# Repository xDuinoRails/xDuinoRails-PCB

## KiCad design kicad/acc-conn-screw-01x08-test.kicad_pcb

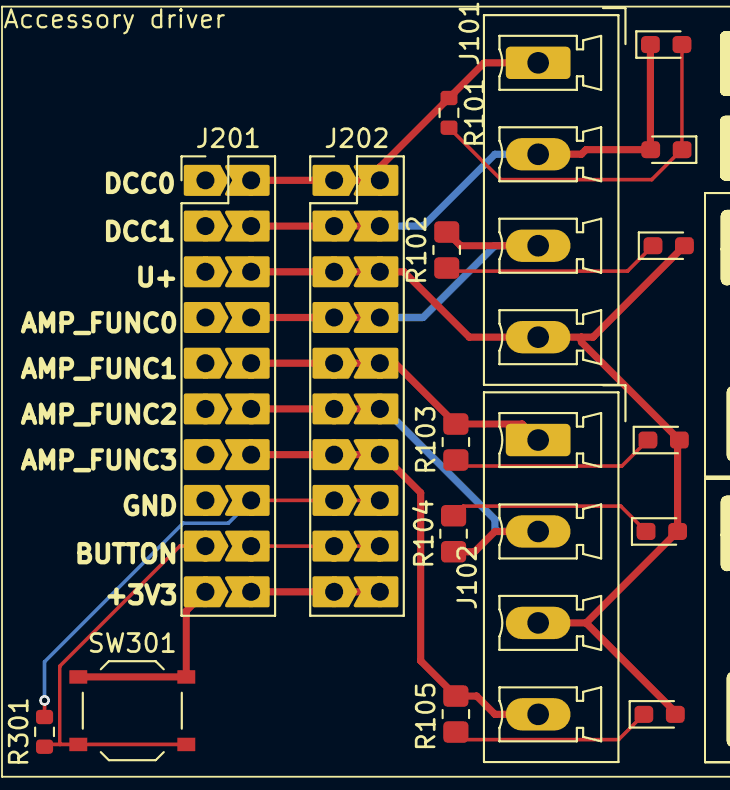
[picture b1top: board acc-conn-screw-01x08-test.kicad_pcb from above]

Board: 2 copper layers, 17 parts (0 on the bottom side), 17 nets.

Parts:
D101: LED_YELLOW; LED_0603_1608Metric_Pad1.05x0.95mm_HandSolder
D102: LED_WHITE; LED_0603_1608Metric_Pad1.05x0.95mm_HandSolder
D103, D105: LED_RED; LED_0603_1608Metric_Pad1.05x0.95mm_HandSolder
D104, D106: LED_GREEN; LED_0603_1608Metric_Pad1.05x0.95mm_HandSolder
J101, J102: Conn_01x04; PhoenixContact_MCV_1,5_4-G-5.08_1x04_P5.08mm_Vertical
J201, J202: Conn_02x10_Odd_Even; PinHeaderJP_2x10_P2.54mm_Vertical
R101, R301: 10k; R_0603_1608Metric
R102, R103, R104, R105: 1k; R_0805_2012Metric_Pad1.20x1.40mm_HandSolder
SW301: TS-1187A-B-A-B; SW_Push_1P1T_XKB_TS-1187A

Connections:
/+3V3: J201.19, SW301.1
/BUTTON: J201.17, R301.1, SW301.2
/J_+3V3: J201.20, J202.19, J202.20
/J_AMP_FUNC0: J101.3, J201.8, J202.7, J202.8, R102.1
/J_AMP_FUNC1: J102.1, J201.10, J202.9, J202.10, R103.1
/J_AMP_FUNC2: J102.2, J201.12, J202.11, J202.12, R104.1
/J_AMP_FUNC3: J102.4, J201.14, J202.13, J202.14, R105.1
/J_BUTTON: J201.18, J202.17, J202.18
/J_DCC0: J101.1, J201.2, J202.1, J202.2, R101.1
/J_DCC1: D101.2 (A), D102.1 (K), J101.2, J201.4, J202.3, J202.4
/J_GND: J201.16, J202.15, J202.16, R301.2
/J_U+: D103.2 (A), D104.2 (A), D105.2 (A), D106.2 (A), J101.4, J102.3, J201.6, J202.5, J202.6
unnamed: D101.1 (K), D102.2 (A), R101.2
unnamed: D103.1 (K), R102.2
unnamed: D104.1 (K), R103.2
unnamed: D105.1 (K), R104.2
unnamed: D106.1 (K), R105.2

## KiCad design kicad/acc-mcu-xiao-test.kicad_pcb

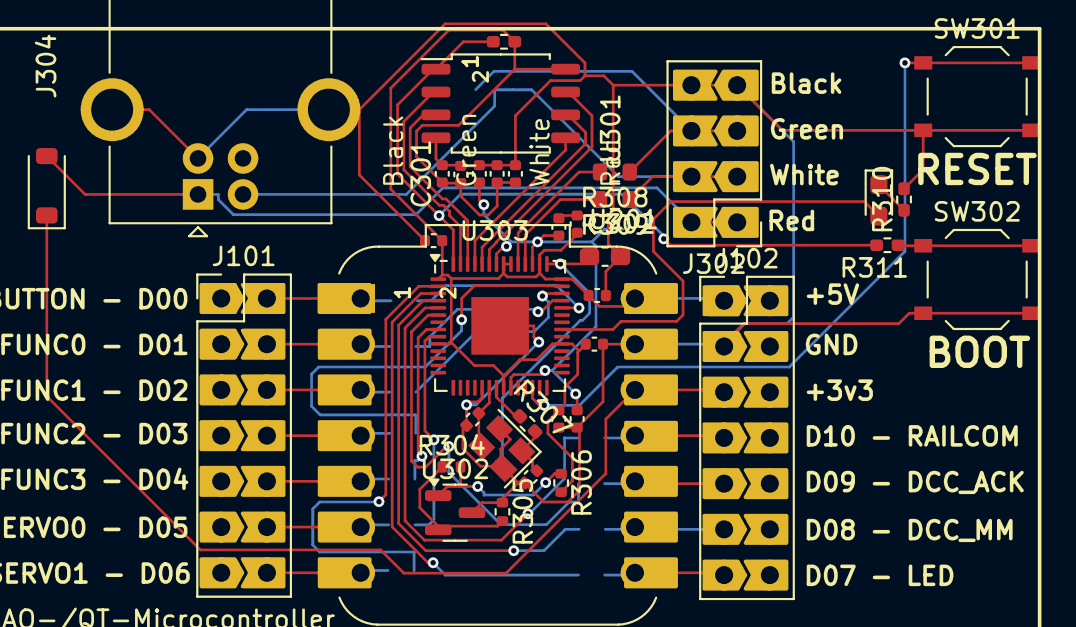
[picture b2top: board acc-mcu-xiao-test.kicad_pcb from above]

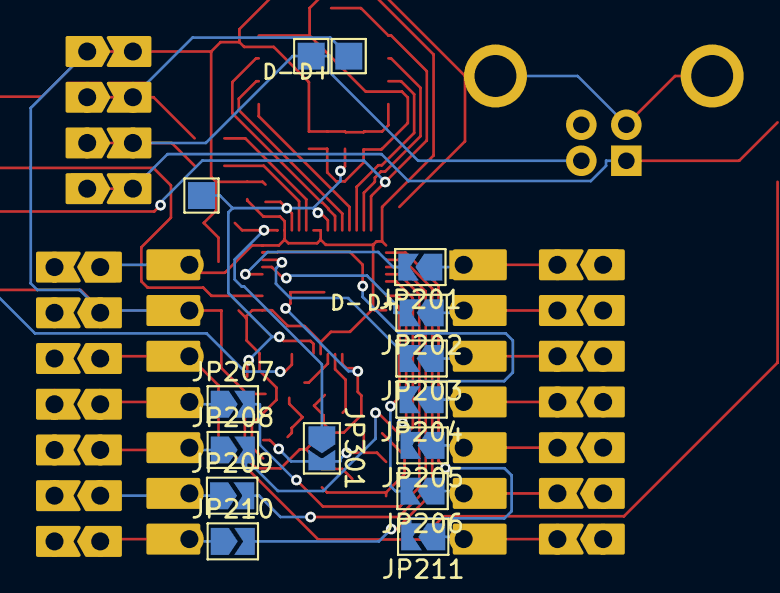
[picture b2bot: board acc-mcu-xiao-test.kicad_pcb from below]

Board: 2 copper layers, 52 parts (15 on the bottom side), 47 nets.

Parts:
C301, C305, C306, C308, C310, C311, C312, C313, C314, C315: 100n; C_0402_1005Metric
C302: 10n C0G; C_0603_1608Metric_Pad1.08x0.95mm_HandSolder
C303, C304: 18p; C_0402_1005Metric
C307, C309: 1u; C_0402_1005Metric
D301: B5819W; D_SOD-123
D302: LED; LED_0603_1608Metric_Pad1.05x0.95mm_HandSolder
J101, J102: Conn_02x07_Odd_Even; PinHeaderJP_2x07_P2.54mm_Vertical
J302: Conn_02x04_Odd_Even; PinHeaderJP_2x04_P2.54mm_Vertical
J304: USB_B; USB_B_OST_USB-B1HSxx_Horizontal
JP201, JP202, JP203, JP204, JP205, JP206, JP207, JP208, JP209, JP210, JP211: SolderJumper_2_Open; SolderJumper-2_P1.3mm_Open_TrianglePad1.0x1.5mm
JP301: VREF; SolderJumper-2_P1.3mm_Open_TrianglePad1.0x1.5mm
R301: DNP; R_0402_1005Metric_Pad0.72x0.64mm_HandSolder
R304: 680R; R_0402_1005Metric
R305: 3k3; R_0402_1005Metric
R306: 150R; R_0402_1005Metric
R307, R310, R311: 1k; R_0402_1005Metric_Pad0.72x0.64mm_HandSolder
R308, R309: 27R; R_0603_1608Metric
SW301: RESET; SW_Push_1P1T_XKB_TS-1187A
SW302: BOOTSEL; SW_Push_1P1T_XKB_TS-1187A
TP301: VREG; TestPoint_Pad_1.5x1.5mm
TP302: D+; TestPoint_Pad_1.5x1.5mm
TP303: D-; TestPoint_Pad_1.5x1.5mm
U201: MOUDLE-SEEEDUINO-XIAO-ESP32C3; XIAO_THT_SMD
U301: W25Q128JVSIQ; SOIC-8_5.23x5.23mm_P1.27mm
U302: TL431DBZ; SOT-23
U303: RP2040; QFN-56-1EP_7x7mm_P0.4mm_EP3.2x3.2mm
Y301: ECS-120-12-36-AGN-TR3; Crystal_SMD_2520-4Pin_2.5x2.0mm

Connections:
+1V1: C305.1, C306.1, C307.1, TP301.1, U303.23 (DVDD), U303.45 (VREG_VOUT), U303.50 (DVDD)
+5V: D301.1 (K), J102.5, U201.12 (3V3)
/J_+3v3: C301.1, C308.1, C309.1, C310.1, C311.1, C312.1, C313.1, C314.1, C315.1, J102.1, R301.1, R306.2, U201.14 (5V), U301.8 (VCC), U303.1 (IOVDD), U303.10 (IOVDD), U303.22 (IOVDD), U303.33 (IOVDD), U303.42 (IOVDD), U303.44 (VREG_IN), U303.48 (USB_VDD), U303.49 (IOVDD)
/J_BUTTON: J101.2, JP201.1 (A), U201.1 (A0)
/J_DCC_ACK: J102.11, JP209.1 (A), U201.9 (A8_SCK)
/J_DCC_MM: J102.13, JP210.1 (A), U201.8 (A7_RX)
/J_FUNC0: J101.4, JP202.1 (A), U201.2 (A1)
/J_FUNC1: J101.6, JP203.1 (A), U201.3 (A2)
/J_FUNC2: J101.8, JP204.1 (A), U201.4 (A3)
/J_FUNC3: J101.10, JP205.1 (A), U201.5 (A4_SDA)
/J_GND: C301.2, C302.2, C303.2, C304.2, C305.2, C306.2, C307.2, C308.2, C309.2, C310.2, C311.2, C312.2, C313.2, C314.2, C315.2, J102.3, J302.7, J302.8, J304.4 (GND), J304.5 (Shield), R305.1, R310.2, SW301.2, SW302.2, U201.13 (GND), U301.4 (GND), U302.3 (A), U303.19 (TESTEN), U303.57 (GND), Y301.2, Y301.4
/J_LED: J102.7, JP207.1 (A), U201.11 (A10_MOSI)
/J_RAILCOM: J102.9, JP208.1 (A), U201.10 (A9_MISO)
/J_SERVO0: J101.12, JP206.1 (A), U201.6 (A5_SCL)
/J_SERVO1: J101.14, JP211.1 (A), U201.7 (A6_TX)
/acc-mcu-xiao/GPIO0: JP211.2 (B), U303.2 (GPIO0)
/acc-mcu-xiao/GPIO1: JP210.2 (B), U303.3 (GPIO1)
/acc-mcu-xiao/GPIO2: JP209.2 (B), U303.4 (GPIO2)
/acc-mcu-xiao/GPIO3: JP207.2 (B), U303.5 (GPIO3)
/acc-mcu-xiao/GPIO4: JP208.2 (B), U303.6 (GPIO4)
/acc-mcu-xiao/GPIO6: JP205.2 (B), U303.8 (GPIO6)
/acc-mcu-xiao/GPIO7: JP206.2 (B), U303.9 (GPIO7)
/acc-mcu-xiao/GPIO23: D302.2 (A), U303.35 (GPIO23)
/acc-mcu-xiao/GPIO26: JP201.2 (B), U303.38 (GPIO26_ADC0)
/acc-mcu-xiao/GPIO27: JP202.2 (B), U303.39 (GPIO27_ADC1)
/acc-mcu-xiao/GPIO28: JP203.2 (B), U303.40 (GPIO28_ADC2)
/acc-mcu-xiao/GPIO29: JP204.2 (B), U303.41 (GPIO29_ADC3)
/acc-mcu-xiao/mcu_rp2040-onboard/2v5_VREF: R304.1, R305.2, U302.2 (REF)
/acc-mcu-xiao/mcu_rp2040-onboard/3V0_VREF: JP301.2 (B), R304.2, R306.1, U302.1 (K)
/acc-mcu-xiao/mcu_rp2040-onboard/ADC_VREF: C302.1, JP301.1 (A), U303.43 (ADC_AVDD)
/acc-mcu-xiao/mcu_rp2040-onboard/D+: J302.5, J302.6, R308.1, TP302.1
/acc-mcu-xiao/mcu_rp2040-onboard/D-: J302.3, J302.4, J304.2 (D-), R309.1, TP303.1
/acc-mcu-xiao/mcu_rp2040-onboard/DN: R309.2, U303.46 (USB_DM)
/acc-mcu-xiao/mcu_rp2040-onboard/DP: R308.2, U303.47 (USB_DP)
/acc-mcu-xiao/mcu_rp2040-onboard/QSPI_SCLK: U301.6 (CLK), U303.52 (QSPI_SCLK)
/acc-mcu-xiao/mcu_rp2040-onboard/QSPI_SD0: U301.5 (DI(IO0)), U303.53 (QSPI_SD0)
/acc-mcu-xiao/mcu_rp2040-onboard/QSPI_SD1: U301.2 (DO(IO1)), U303.55 (QSPI_SD1)
/acc-mcu-xiao/mcu_rp2040-onboard/QSPI_SD2: U301.3 (IO2), U303.54 (QSPI_SD2)
/acc-mcu-xiao/mcu_rp2040-onboard/QSPI_SD3: U301.7 (IO3), U303.51 (QSPI_SD3)
/acc-mcu-xiao/mcu_rp2040-onboard/QSPI_SS: R301.2, R311.1, U301.1 (~CS), U303.56 (QSPI_SS)
/acc-mcu-xiao/mcu_rp2040-onboard/RESET_RUN: SW301.1, U303.26 (RUN)
/acc-mcu-xiao/mcu_rp2040-onboard/XIN: C303.1, U303.20 (XIN), Y301.3
/acc-mcu-xiao/mcu_rp2040-onboard/XOUT: R307.1, U303.21 (XOUT)
unnamed: C304.1, R307.2, Y301.1
unnamed: D302.1 (K), R310.1
unnamed: R311.2, SW302.1
VBUS: D301.2 (A), J302.1, J302.2, J304.1 (VBUS)

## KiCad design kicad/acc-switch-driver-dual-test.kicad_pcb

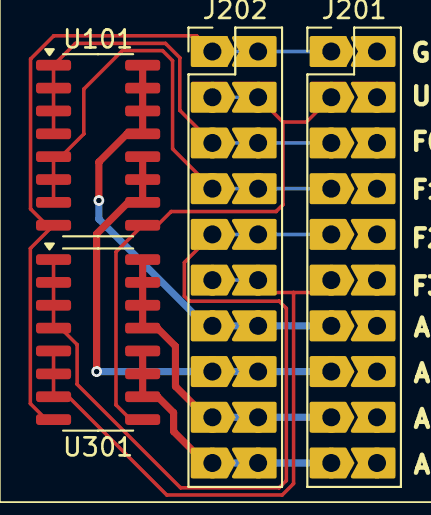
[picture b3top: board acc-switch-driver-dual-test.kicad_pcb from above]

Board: 2 copper layers, 4 parts (0 on the bottom side), 10 nets.

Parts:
J201, J202: Conn_02x10_Odd_Even; PinHeaderJP_2x10_P2.54mm_Vertical
U101, U301: ULN2003A; SOIC-16_3.9x9.9mm_P1.27mm

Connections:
/J_AMP_FUNC0: J201.13, J202.13, J202.14, U101.13 (O4), U101.14 (O3), U101.15 (O2), U101.16 (O1)
/J_AMP_FUNC1: J201.15, J202.15, J202.16, U101.10 (O7), U101.11 (O6), U101.12 (O5)
/J_AMP_FUNC2: J201.17, J202.17, J202.18, U301.13 (O4), U301.14 (O3), U301.15 (O2), U301.16 (O1)
/J_AMP_FUNC3: J201.19, J202.19, J202.20, U301.10 (O7), U301.11 (O6), U301.12 (O5)
/J_FUNC0: J201.5, J202.5, J202.6, U101.1 (I1), U101.2 (I2), U101.3 (I3), U101.4 (I4)
/J_FUNC1: J201.7, J202.7, J202.8, U101.5 (I5), U101.6 (I6), U101.7 (I7)
/J_FUNC2: J201.9, J202.9, J202.10, U301.1 (I1), U301.2 (I2), U301.3 (I3), U301.4 (I4)
/J_FUNC3: J201.11, J202.11, J202.12, U301.5 (I5), U301.6 (I6), U301.7 (I7)
/J_GND: J201.1, J202.1, J202.2, U101.8 (GND), U301.8 (GND)
/J_U+: J201.3, J202.3, J202.4, U101.9 (COM), U301.9 (COM)

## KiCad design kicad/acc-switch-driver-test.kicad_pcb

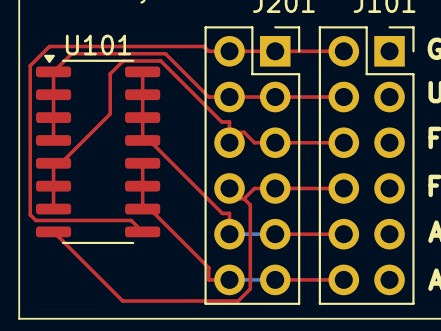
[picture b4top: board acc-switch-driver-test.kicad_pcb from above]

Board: 2 copper layers, 3 parts (0 on the bottom side), 6 nets.

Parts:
J101, J201: Conn_02x06_Odd_Even; PinSocket_2x06_P2.54mm_Vertical
U101: ULN2003A; SOIC-16_3.9x9.9mm_P1.27mm

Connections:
/J_AMP_FUNC0: J101.10, J201.9, J201.10, U101.13 (O4), U101.14 (O3), U101.15 (O2), U101.16 (O1)
/J_AMP_FUNC1: J101.12, J201.11, J201.12, U101.10 (O7), U101.11 (O6), U101.12 (O5)
/J_FUNC0: J101.4, J201.3, J201.4, U101.1 (I1), U101.2 (I2), U101.3 (I3), U101.4 (I4)
/J_FUNC1: J101.6, J201.5, J201.6, U101.5 (I5), U101.6 (I6), U101.7 (I7)
/J_GND: J101.8, J201.7, J201.8, U101.8 (GND)
/J_U+: J101.2, J201.1, J201.2, U101.9 (COM)

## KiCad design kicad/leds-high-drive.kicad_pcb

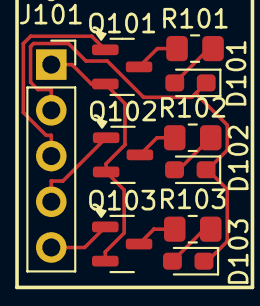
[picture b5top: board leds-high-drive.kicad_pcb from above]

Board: 2 copper layers, 10 parts (0 on the bottom side), 11 nets.

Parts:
D101: LED_RED; LED_0603_1608Metric_Pad1.05x0.95mm_HandSolder
D102: LED_YELLOW; LED_0603_1608Metric_Pad1.05x0.95mm_HandSolder
D103: LED_GREEN; LED_0603_1608Metric_Pad1.05x0.95mm_HandSolder
J101: Conn_01x05; PinSocket_1x05_P2.54mm_Vertical
Q101, Q102, Q103: S8550; 8x50_SOT-23
R101, R102, R103: 1k; R_0805_2012Metric_Pad1.20x1.40mm_HandSolder

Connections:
/+3v3: J101.1, Q101.1 (E), Q102.1 (E), Q103.1 (E)
/GND: D101.1 (K), D102.1 (K), D103.1 (K), J101.2
/LED1: J101.3, Q101.2 (B)
/LED2: J101.4, Q102.2 (B)
/LED3: J101.5, Q103.2 (B)
unnamed: D101.2 (A), R101.2
unnamed: D102.2 (A), R102.2
unnamed: D103.2 (A), R103.2
unnamed: Q101.3 (C), R101.1
unnamed: Q102.3 (C), R102.1
unnamed: Q103.3 (C), R103.1
